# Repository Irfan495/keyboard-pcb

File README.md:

# keyboard-pcb
 pcb for mechanical keyboard

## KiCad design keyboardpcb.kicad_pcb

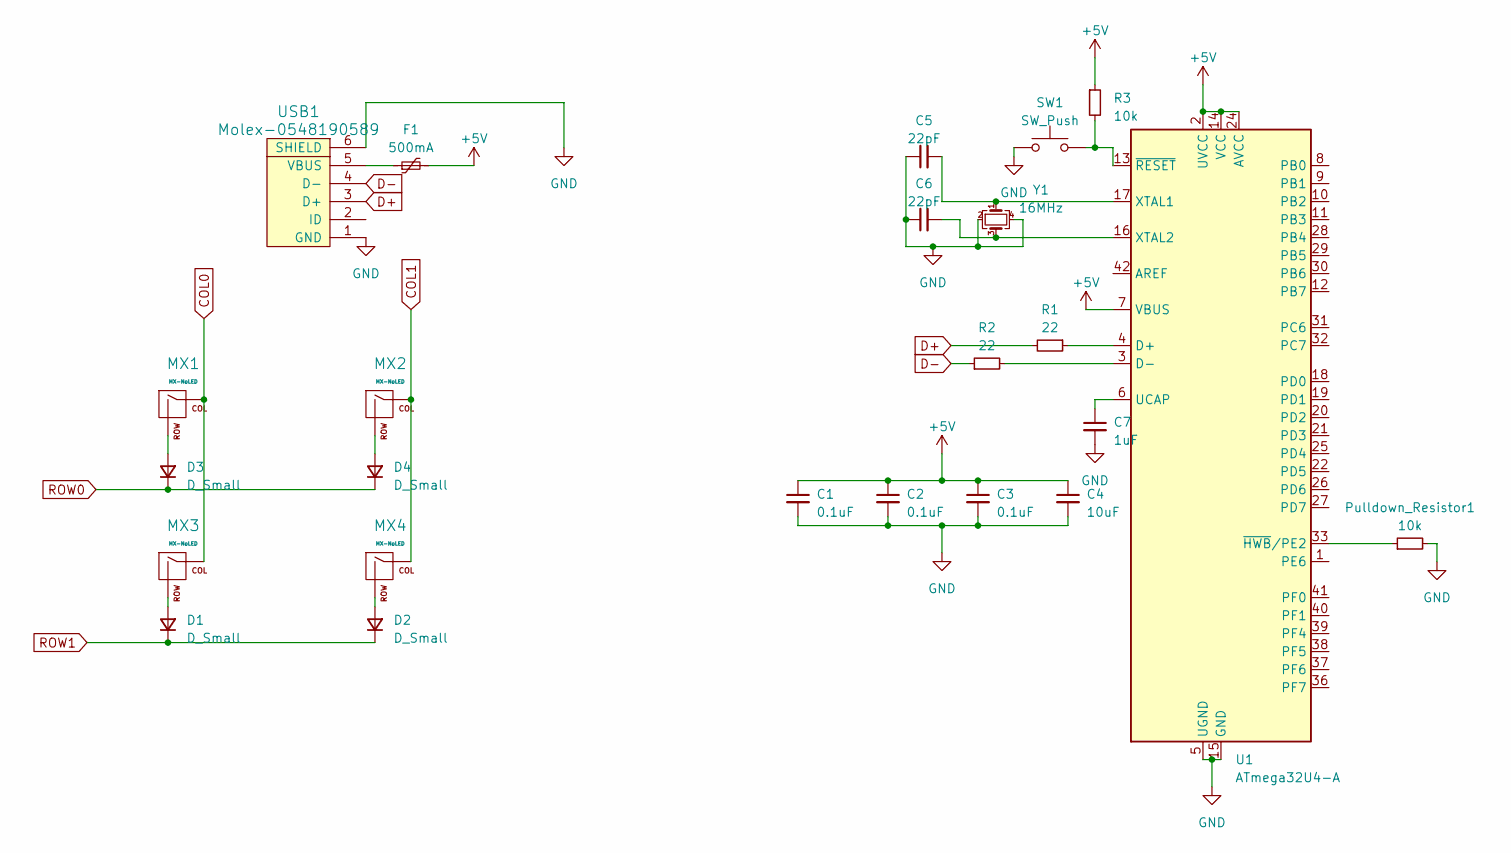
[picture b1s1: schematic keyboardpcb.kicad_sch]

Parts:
C1, C2, C3: 0.1uF; C_0805_2012Metric
C4: 10uF; C_0805_2012Metric
C5, C6: 22pF; C_0805_2012Metric
C7: 1uF; C_0805_2012Metric
D1, D2, D3, D4: D_Small; D_SOD-123
F1: 500mA; Fuse_1206_3216Metric
MX1, MX2, MX3, MX4: MX-NoLED; MX-1U
Pulldown_Resistor1: 10k; R_0805_2012Metric
R1, R2: 22; R_0805_2012Metric
R3: 10k; R_0805_2012Metric
SW1: SW_Push; SKQG-1155865
U1: ATmega32U4-A; TQFP-44_10x10mm_P0.8mm
USB1: Molex-0548190589
Y1: 16MHz; Crystal_SMD_3225-4Pin_3.2x2.5mm

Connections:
+5V: C1.1, C2.1, C3.1, C4.1, F1.2, R3.1, U1.2 (UVCC), U1.7 (VBUS), U1.14 (VCC), U1.24 (AVCC), U1.34 (VCC), U1.44 (AVCC)
COL0: MX1.1 (COL), MX3.1 (COL)
COL1: MX2.1 (COL), MX4.1 (COL)
D+: R1.2, USB1.3 (D+)
D-: R2.1, USB1.4 (D-)
GND: C1.2, C2.2, C3.2, C4.2, C5.1, C6.1, C7.2, Pulldown_Resistor1.2, SW1.1, U1.5 (UGND), U1.15 (GND), U1.23 (GND), U1.35 (GND), U1.43 (GND), USB1.1 (GND), USB1.6 (SHIELD), Y1.2, Y1.4
unnamed: D1.2 (A), MX3.2 (ROW)
unnamed: D2.2 (A), MX4.2 (ROW)
unnamed: D3.2 (A), MX1.2 (ROW)
unnamed: D4.2 (A), MX2.2 (ROW)
unnamed: R1.1, U1.4 (D+)
unnamed: R2.2, U1.3 (D-)
unnamed: C7.1, U1.6 (UCAP)
unnamed: C5.2, U1.17 (XTAL1), Y1.1
unnamed: C6.2, U1.16 (XTAL2), Y1.3
unnamed: Pulldown_Resistor1.1, U1.33 (~HWB/PE2)
unnamed: R3.2, SW1.2, U1.13 (~RESET)
unnamed: F1.1, USB1.5 (VBUS)
ROW0: D3.1 (K), D4.1 (K)
ROW1: D1.1 (K), D2.1 (K)

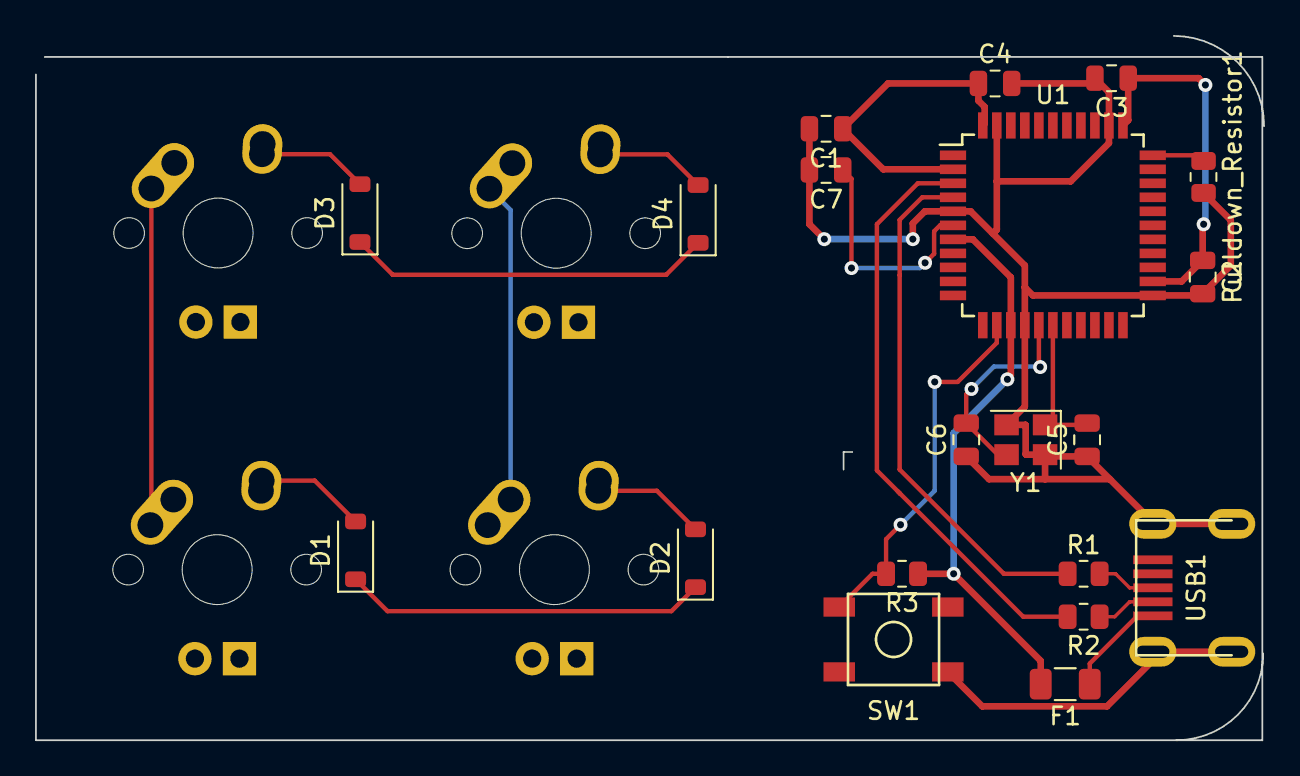
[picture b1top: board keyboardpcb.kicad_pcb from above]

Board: 2 copper layers, 70.1 x 40.2 mm, 24 parts (0 on the bottom side), 20 nets.

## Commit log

2023-02-14 Initialize project
    created kicad files
2023-02-14 Add submoduls
2023-02-14 add footprint libs
2023-02-14 MCU Zone
    added MCU to schematic
2023-02-16 Finished the schematic
    2x2 keyboard schematic for testing
2023-02-16 routed the pcb
2023-02-16 finished pcb routing
